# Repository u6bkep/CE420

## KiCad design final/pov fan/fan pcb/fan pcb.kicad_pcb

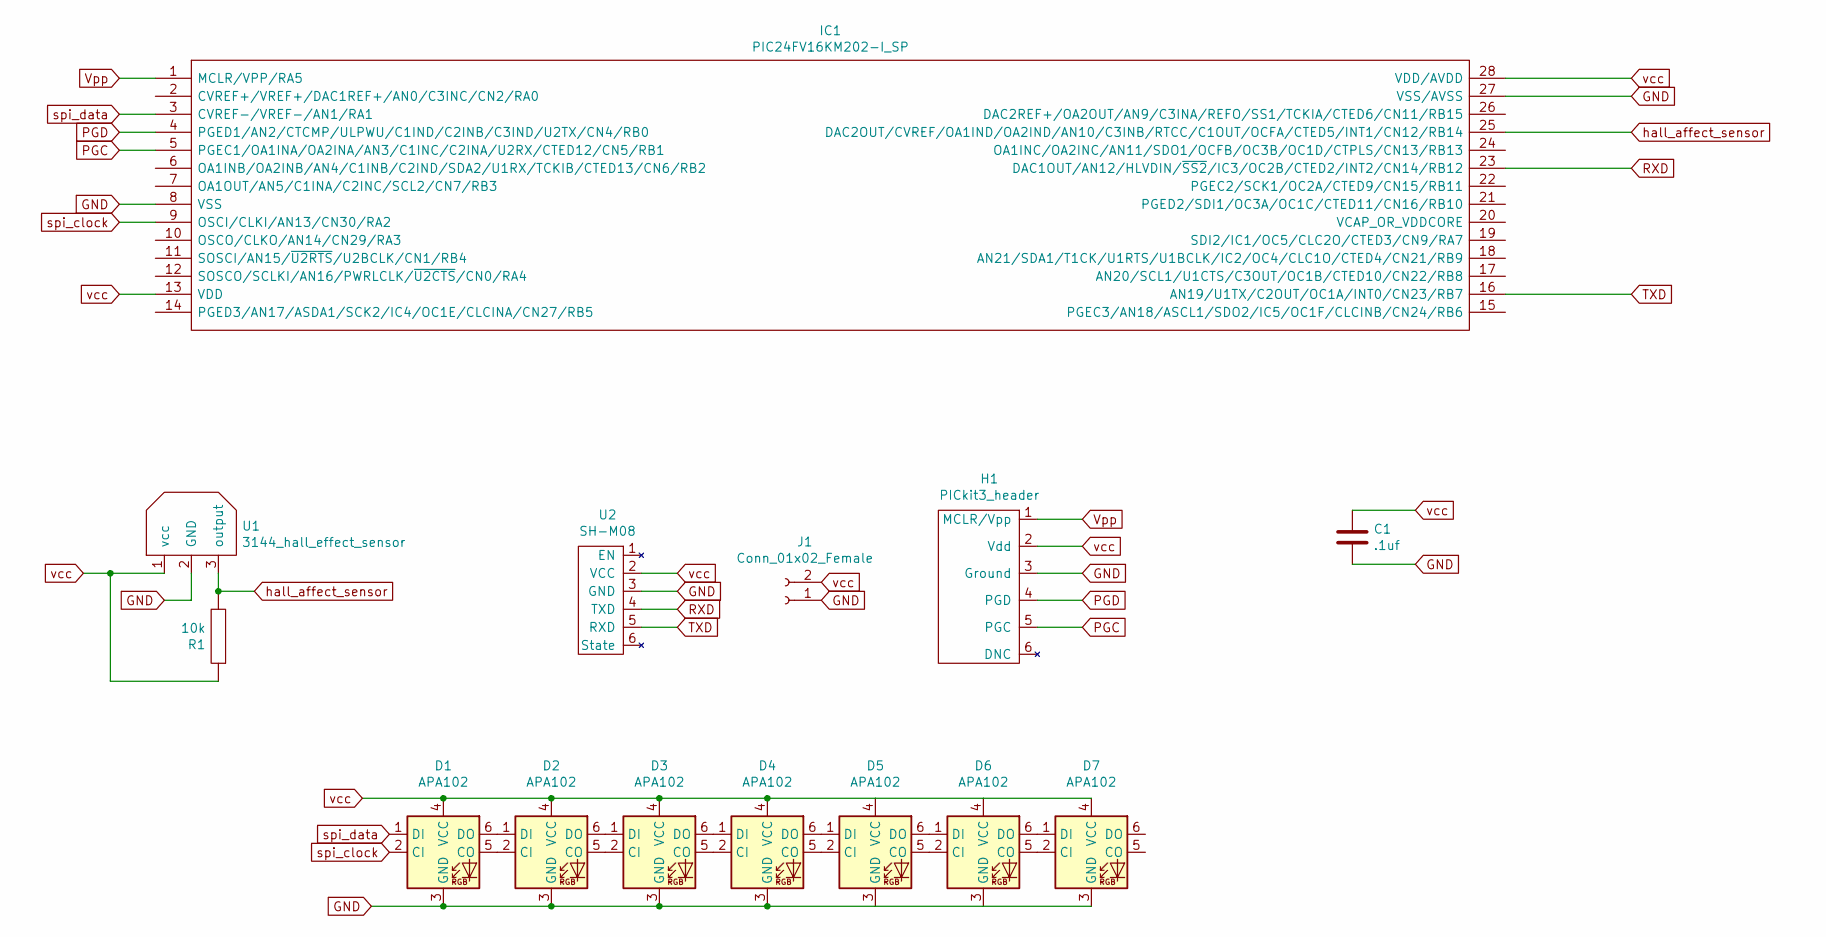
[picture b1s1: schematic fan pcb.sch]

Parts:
C1: .1uf; C_0603_1608Metric
D1, D2, D3, D4, D5, D6, D7: APA102; LED_RGB_5050-6
H1: PICkit3_header; PinHeader_1x06_P2.54mm_Horizontal
IC1: PIC24FV16KM202-I_SP; DIP794W56P254L3486H508Q28N; Manufacturer_Part_Number PIC24FV16KM202-I/SP; Mouser Part Number 579-24FV16KM202I/SP
J1: Conn_01x02_Female; PinHeader_1x02_P2.54mm_Vertical
R1: 10k; R_0603_1608Metric
U1: 3144_hall_effect_sensor; TO-92Flat
U2: SH-M08; PinHeader_1x06_P2.54mm_Horizontal

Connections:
GND: C1.2, D1.3 (GND), D2.3 (GND), D3.3 (GND), D4.3 (GND), D5.3 (GND), D6.3 (GND), D7.3 (GND), H1.3 (Ground), IC1.8 (VSS), IC1.27 (VSS/AVSS), J1.1, U1.2 (GND), U2.3 (GND)
unnamed: D1.5 (CO), D2.2 (CI)
unnamed: D1.6 (DO), D2.1 (DI)
unnamed: D2.5 (CO), D3.2 (CI)
unnamed: D2.6 (DO), D3.1 (DI)
unnamed: D3.5 (CO), D4.2 (CI)
unnamed: D3.6 (DO), D4.1 (DI)
unnamed: D4.5 (CO), D5.2 (CI)
unnamed: D4.6 (DO), D5.1 (DI)
unnamed: D5.5 (CO), D6.2 (CI)
unnamed: D5.6 (DO), D6.1 (DI)
unnamed: D6.5 (CO), D7.2 (CI)
unnamed: D6.6 (DO), D7.1 (DI)
PGC: H1.5 (PGC), IC1.5 (PGEC1/OA1INA/OA2INA/AN3/C1INC/C2INA/U2R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)
PGD: H1.4 (PGD), IC1.4 (PGED1/AN2/CTCMP/ULPWU/C1IND/C2INB/C3IND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)
RXD: IC1.23 (DAC1OUT/AN12/HLVDIN/~SS2~/IC3/OC2B/CTED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), U2.4 (TXD)
TXD: IC1.16 (AN19/U1TX/C2OUT/OC1A/INT0/CN23/RB7), U2.5 (RXD)
Vpp: H1.1 (MCLR/Vpp), IC1.1 (MCLR/VPP/RA5)
hall_affect_sensor: IC1.25 (DAC2OUT/CVREF/OA1IND/OA2IND/AN10/C3INB/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), R1.2, U1.3 (output)
spi_clock: D1.2 (CI), IC1.9 (OSCI/CLKI/AN13/CN30/RA2)
spi_data: D1.1 (DI), IC1.3 (CVREF-/VREF-/AN1/RA1)
vcc: C1.1, D1.4 (VCC), D2.4 (VCC), D3.4 (VCC), D4.4 (VCC), D5.4 (VCC), D6.4 (VCC), D7.4 (VCC), H1.2 (Vdd), IC1.13 (VDD), IC1.28 (VDD/AVDD), J1.2, R1.1, U1.1 (vcc), U2.2 (VCC)

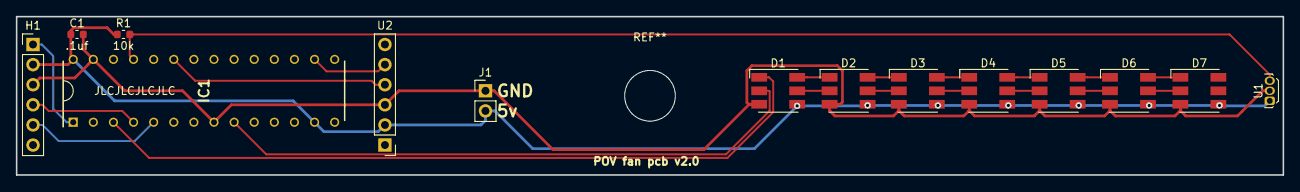
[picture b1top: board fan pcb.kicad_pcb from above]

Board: 2 copper layers, 160.0 x 20.0 mm, 14 parts (0 on the bottom side), 22 nets.

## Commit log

2019-10-31 inital commit
2019-10-31 created report for lab 3
2019-11-07 FInished Code
    Finished the code based on what was required for Lab4. Help from Alex & Caleb when stuck.
2019-11-07 finnished code for lab 4
2019-11-07 Lab4 Submit Files
    Files needed for blackboard.
2019-11-07 Lab05 Init Push
2019-11-07 created lab05 project folder
2019-11-07 Updated 7 seg to provided.
2019-11-07 added output and project files to git ignore
2019-11-07 added base for lab05 and removed ignored files
2019-11-07 Reverted?
2019-11-07 Fixed
2019-11-08 fixed lab 4 cover page labled as lab 3
2019-11-13 basic test of 7 segment display
2019-11-14 wrote 7seg driver and settup timer 2
2019-11-14 finished first pass lab 5
2019-11-14 Submission Info
2019-11-14 added beepper to timer and updated submission docs
2019-11-21 worked on sonar... its all broken...
2019-11-26 switched sonar echo timer to 32 bits\nadded execution time tracking to sonarDistance()
2019-12-04 Added report
2019-12-04 Partially finished
2019-12-05 Deliverables
    I finished as much as possible in the report. I say send it!
2019-12-22 added all data from final project
